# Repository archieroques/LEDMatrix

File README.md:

# LEDMatrix
An LED Matrix project, originally completed for a Gold CREST award. 

All stuff is Open Source - Released under CC-BY-SA-NC 3.0

Matrix isn't necessarily 100% working - you were warned - no guarantees!

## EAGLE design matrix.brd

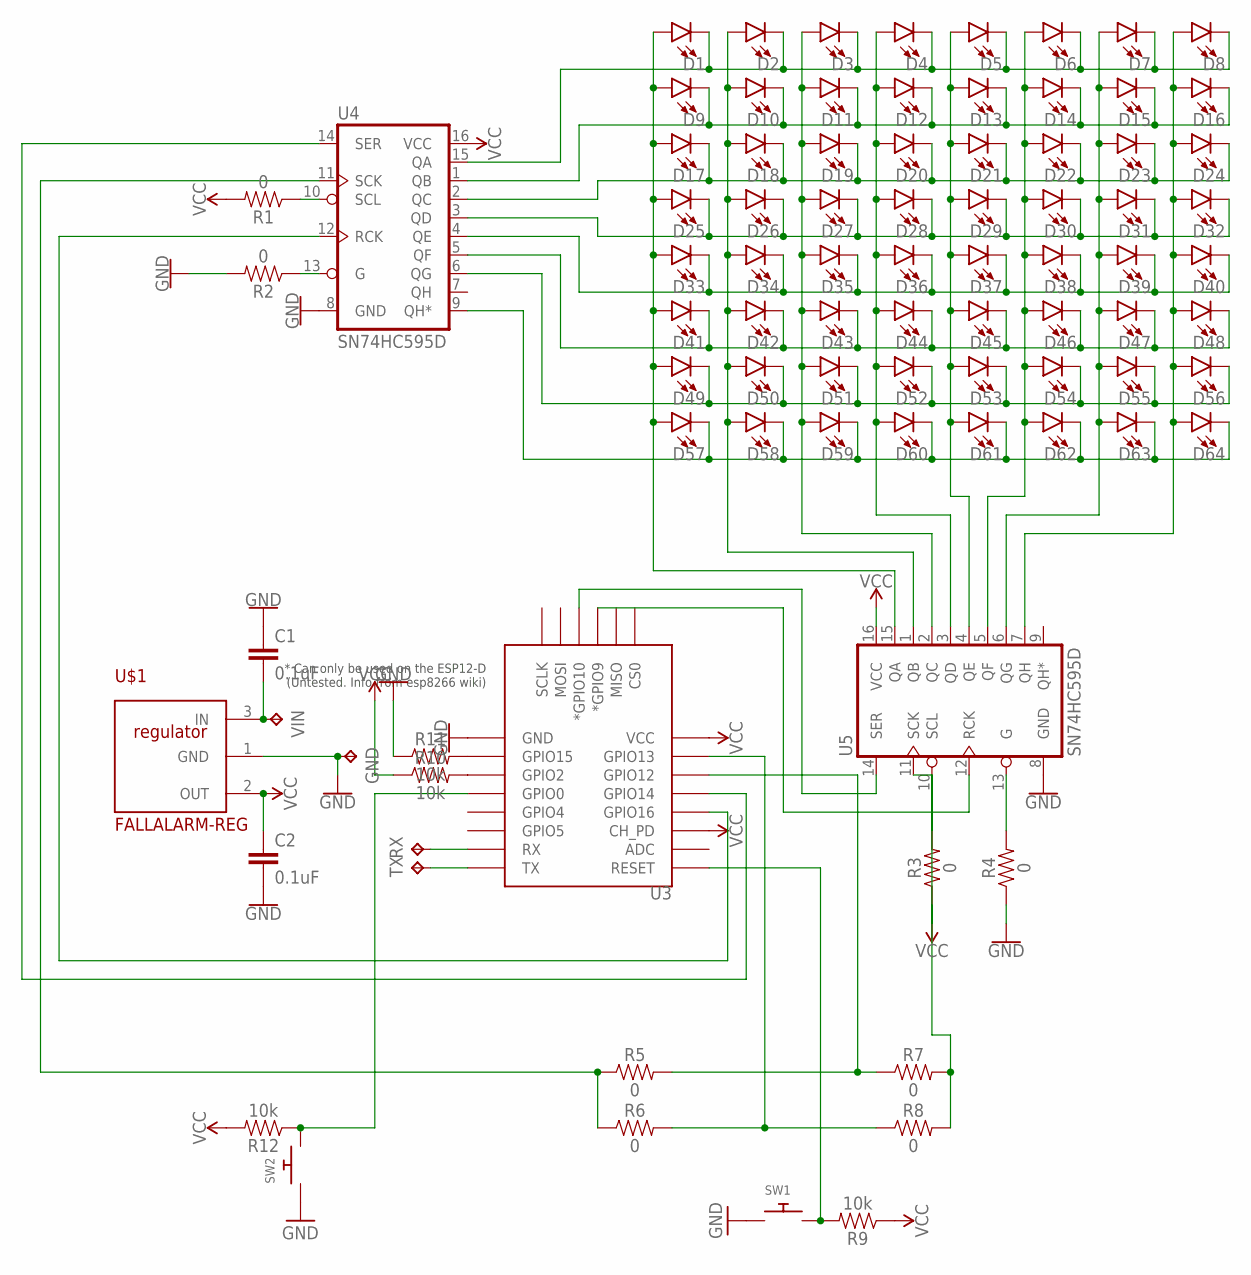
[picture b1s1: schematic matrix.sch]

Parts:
C1, C2: 0.1uF; 0603
D1, D2, D3, D4, D5, D6, D7, D8, D9, D10, D11, D12, D13, D14, D15, D16, D17, D18, D19, D20, D21, D22, D23, D24, D25, D26, D27, D28, D29, D30, D31, D32, D33, D34, D35, D36, D37, D38, D39, D40, D41, D42, D43, D44, D45, D46, D47, D48, D49, D50, D51, D52, D53, D54, D55, D56, D57, D58, D59, D60, D61, D62, D63, D64: LED0603; LED-0603
GND: TPPAD1-17; P1-17
R1, R2, R3, R4, R5, R6, R7, R8: 0; 0603
R9, R10, R11, R12: 10k; 0603
RX: TPTP20SQ; TP20SQ
SW1, SW2: SWITCH_PUSHBUTTONEVQ-PE; TACT_PANA-EVQ
TX: TPTP20SQ; TP20SQ
U3: ESP12ESMD; ESP12E-SMD
U4, U5: SN74HC595D; SO16
U$1: FALLALARM-REG; SOT23
VIN: TPPAD1-17; P1-17

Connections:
GND: C1.1, C2.2, GND.TP, R2.2, R4.1, R11.1, SW1.P$1, SW2.P$1, U3.GND, U4.8 (GND), U5.8 (GND), U$1.1 (GND)
unnamed: D1.C, D2.C, D3.C, D4.C, D5.C, D6.C, D7.C, D8.C, U4.15 (QA)
unnamed: TX.TP, U3.TXD0 (TX)
unnamed: D1.A, D9.A, D17.A, D25.A, D33.A, D41.A, D49.A, D57.A, U5.15 (QA)
unnamed: D2.A, D10.A, D18.A, D26.A, D34.A, D42.A, D50.A, D58.A, U5.1 (QB)
unnamed: D3.A, D11.A, D19.A, D27.A, D35.A, D43.A, D51.A, D59.A, U5.2 (QC)
unnamed: D4.A, D12.A, D20.A, D28.A, D36.A, D44.A, D52.A, D60.A, U5.3 (QD)
unnamed: D5.A, D13.A, D21.A, D29.A, D37.A, D45.A, D53.A, D61.A, U5.4 (QE)
unnamed: D6.A, D14.A, D22.A, D30.A, D38.A, D46.A, D54.A, D62.A, U5.5 (QF)
unnamed: D7.A, D15.A, D23.A, D31.A, D39.A, D47.A, D55.A, D63.A, U5.6 (QG)
unnamed: D8.A, D16.A, D24.A, D32.A, D40.A, D48.A, D56.A, D64.A, U5.7 (QH)
unnamed: D17.C, D18.C, D19.C, D20.C, D21.C, D22.C, D23.C, D24.C, U4.2 (QC)
unnamed: D25.C, D26.C, D27.C, D28.C, D29.C, D30.C, D31.C, D32.C, U4.3 (QD)
unnamed: D9.C, D10.C, D11.C, D12.C, D13.C, D14.C, D15.C, D16.C, U4.1 (QB)
unnamed: D33.C, D34.C, D35.C, D36.C, D37.C, D38.C, D39.C, D40.C, U4.4 (QE)
unnamed: D41.C, D42.C, D43.C, D44.C, D45.C, D46.C, D47.C, D48.C, U4.5 (QF)
unnamed: U3.GPIO14, U4.14 (SER)
unnamed: U3.GPIO10 (*GPIO10), U5.14 (SER)
unnamed: U3.GPIO9 (*GPIO9), U5.12 (RCK)
unnamed: U3.GPIO16, U4.12 (RCK)
unnamed: R1.1, U4.10 (SCL)
unnamed: R3.2, U5.10 (SCL)
unnamed: R2.1, U4.13 (G)
unnamed: R4.2, U5.13 (G)
unnamed: R5.1, R6.1, U4.11 (SCK)
unnamed: D57.C, D58.C, D59.C, D60.C, D61.C, D62.C, D63.C, D64.C, U4.9 (QH*)
unnamed: C1.2, U$1.3 (IN), VIN.TP
unnamed: RX.TP, U3.RXD0 (RX)
unnamed: R5.2, R7.1, U3.GPIO12
unnamed: D49.C, D50.C, D51.C, D52.C, D53.C, D54.C, D55.C, D56.C, U4.6 (QG)
unnamed: R10.2, U3.GPIO2
unnamed: R11.2, U3.GPIO15
unnamed: R9.2, SW1.P$2
unnamed: R6.2, R8.1, U3.GPIO13
unnamed: R7.2, R8.2, U5.11 (SCK)
unnamed: R12.1, SW2.P$2, U3.GPIO0
VCC: C2.1, R1.2, R3.1, R9.1, R10.1, R12.2, U3.CH_PD, U3.VCC, U4.16 (VCC), U5.16 (VCC), U$1.2 (OUT)

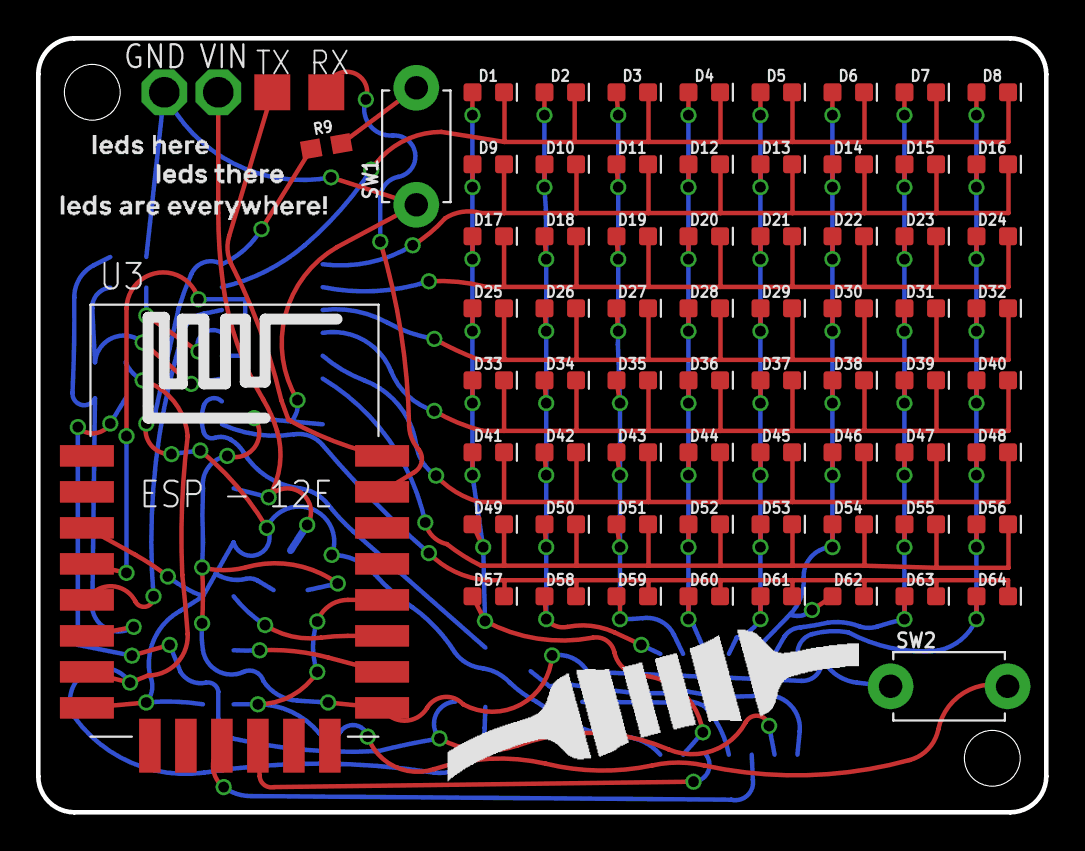
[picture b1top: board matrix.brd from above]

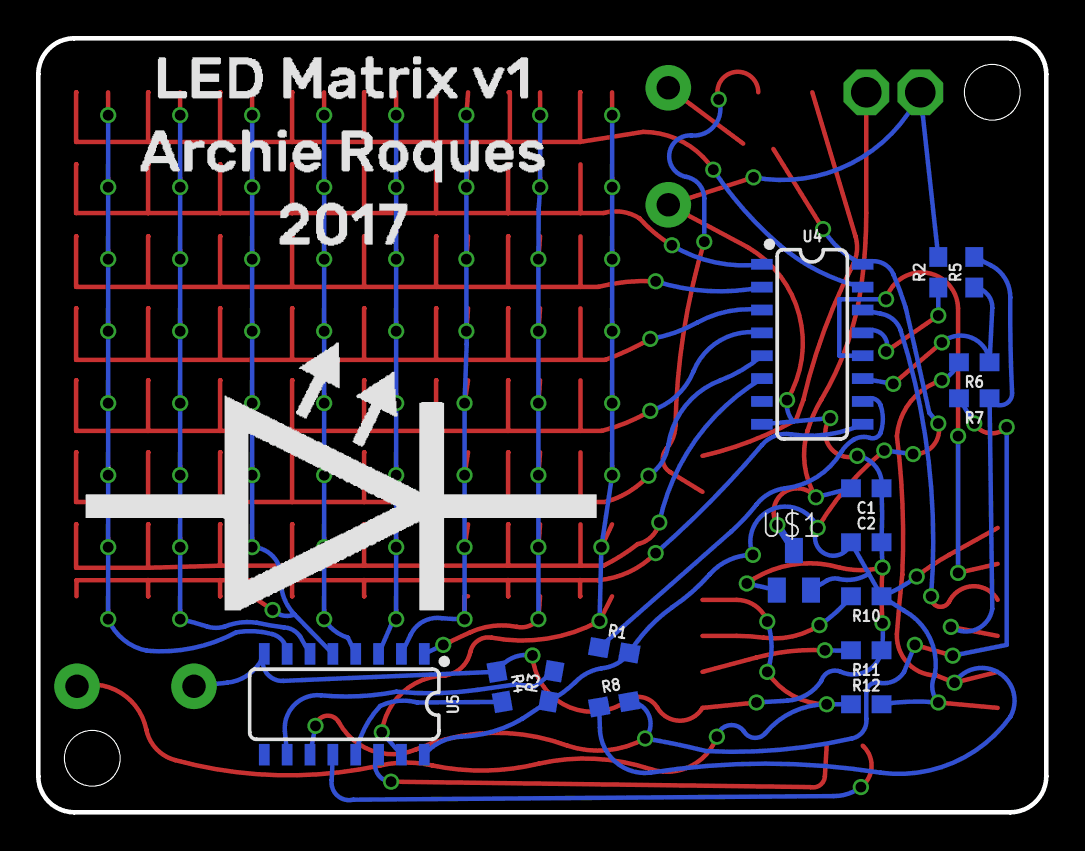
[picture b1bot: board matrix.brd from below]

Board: 2 copper layers, 56.0 x 43.0 mm, 88 parts (16 on the bottom side), 37 nets.

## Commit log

2017-07-20 Added files

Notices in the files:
parts and their libraries:
SparkFun-Capacitors: Licensing: Creative Commons ShareAlike 4.0 International - https://creativecommons.org/licenses/by-sa/4.0
